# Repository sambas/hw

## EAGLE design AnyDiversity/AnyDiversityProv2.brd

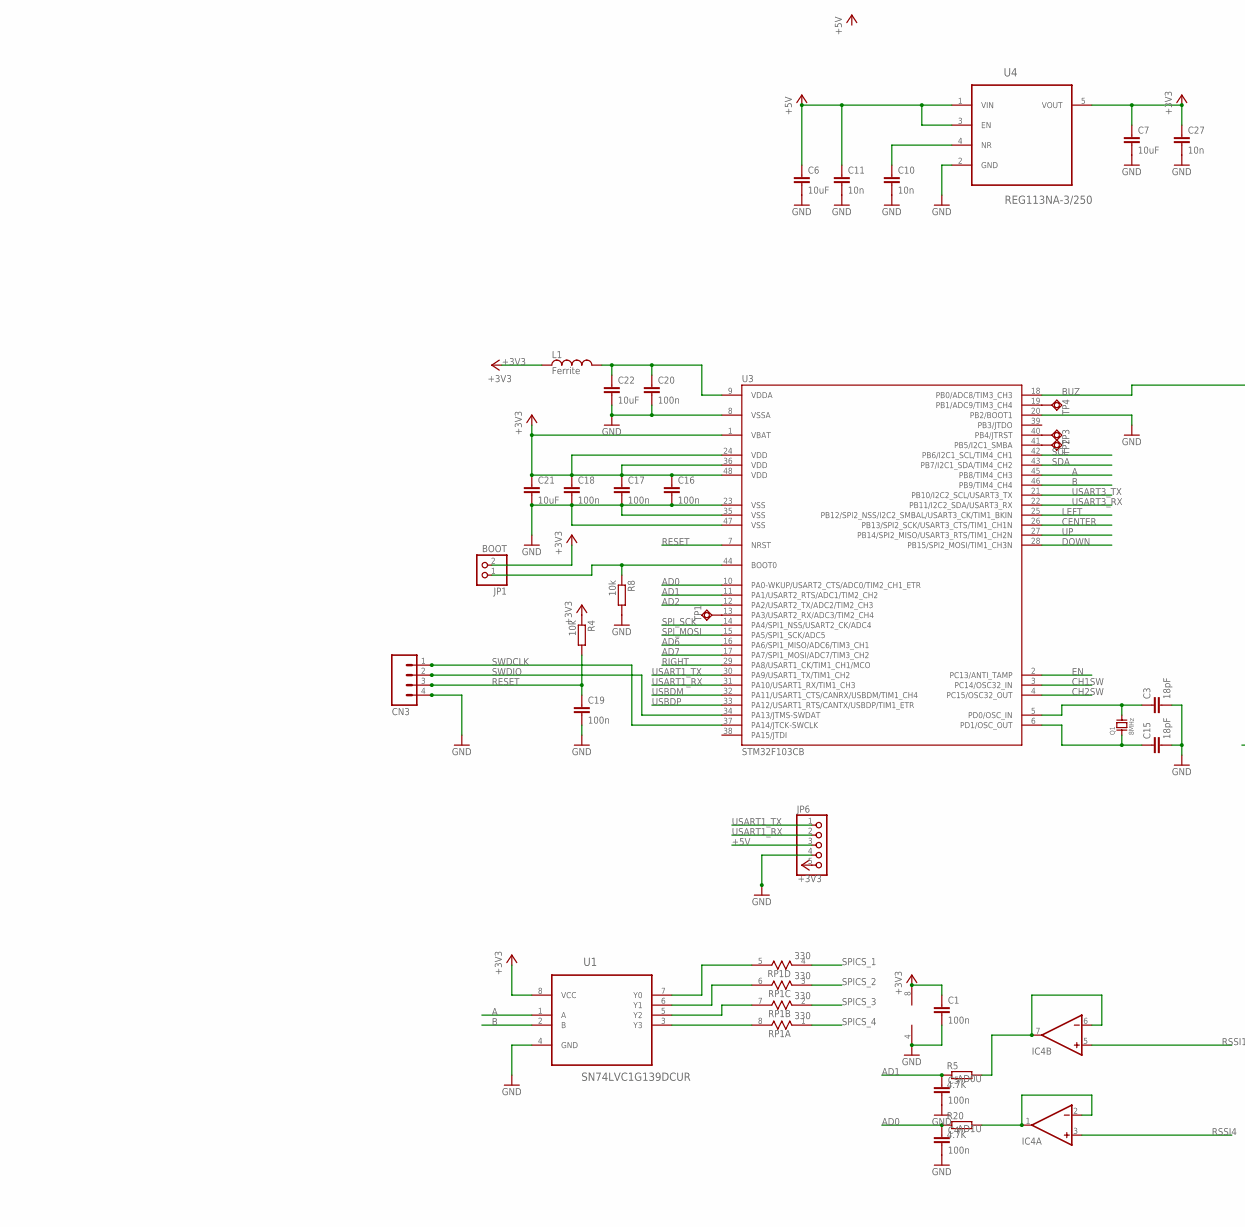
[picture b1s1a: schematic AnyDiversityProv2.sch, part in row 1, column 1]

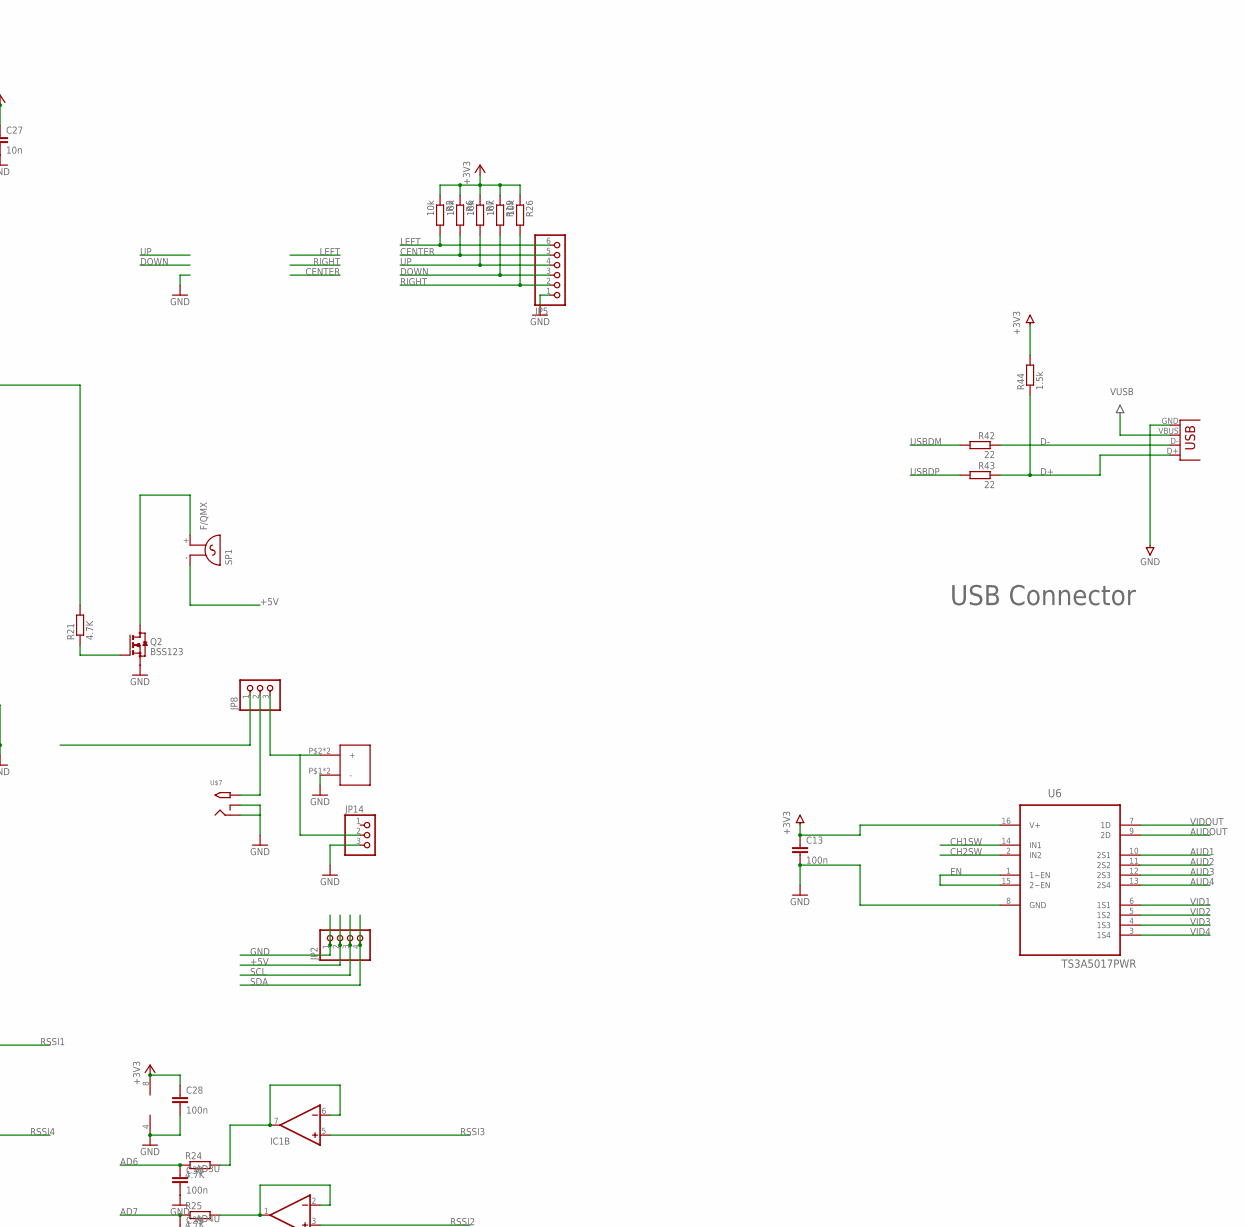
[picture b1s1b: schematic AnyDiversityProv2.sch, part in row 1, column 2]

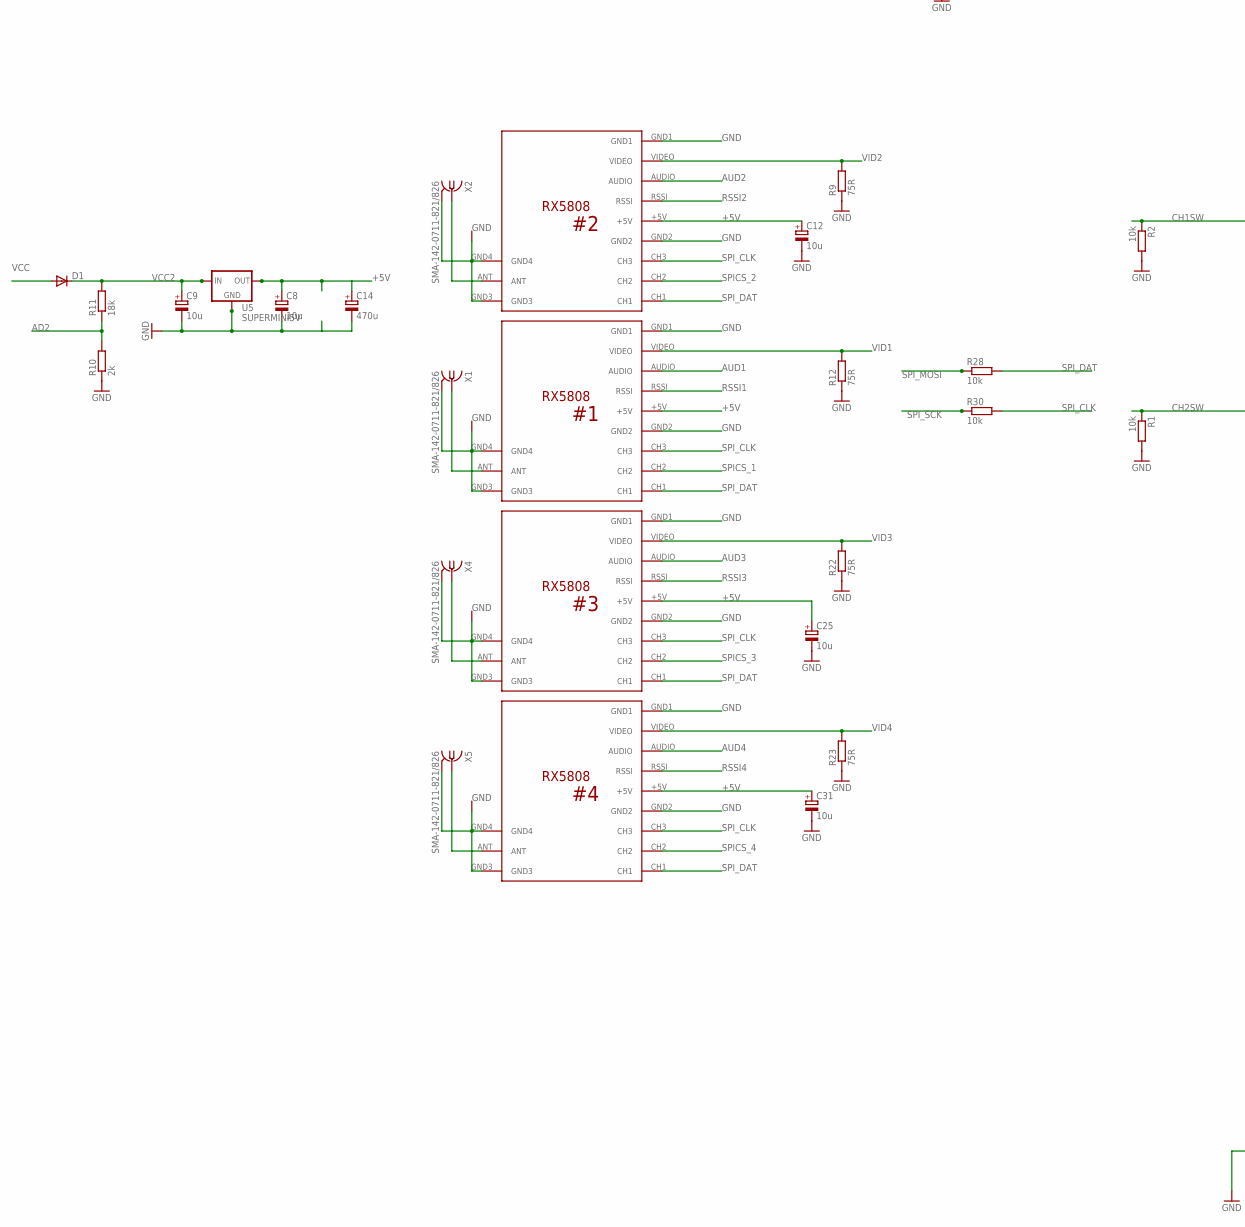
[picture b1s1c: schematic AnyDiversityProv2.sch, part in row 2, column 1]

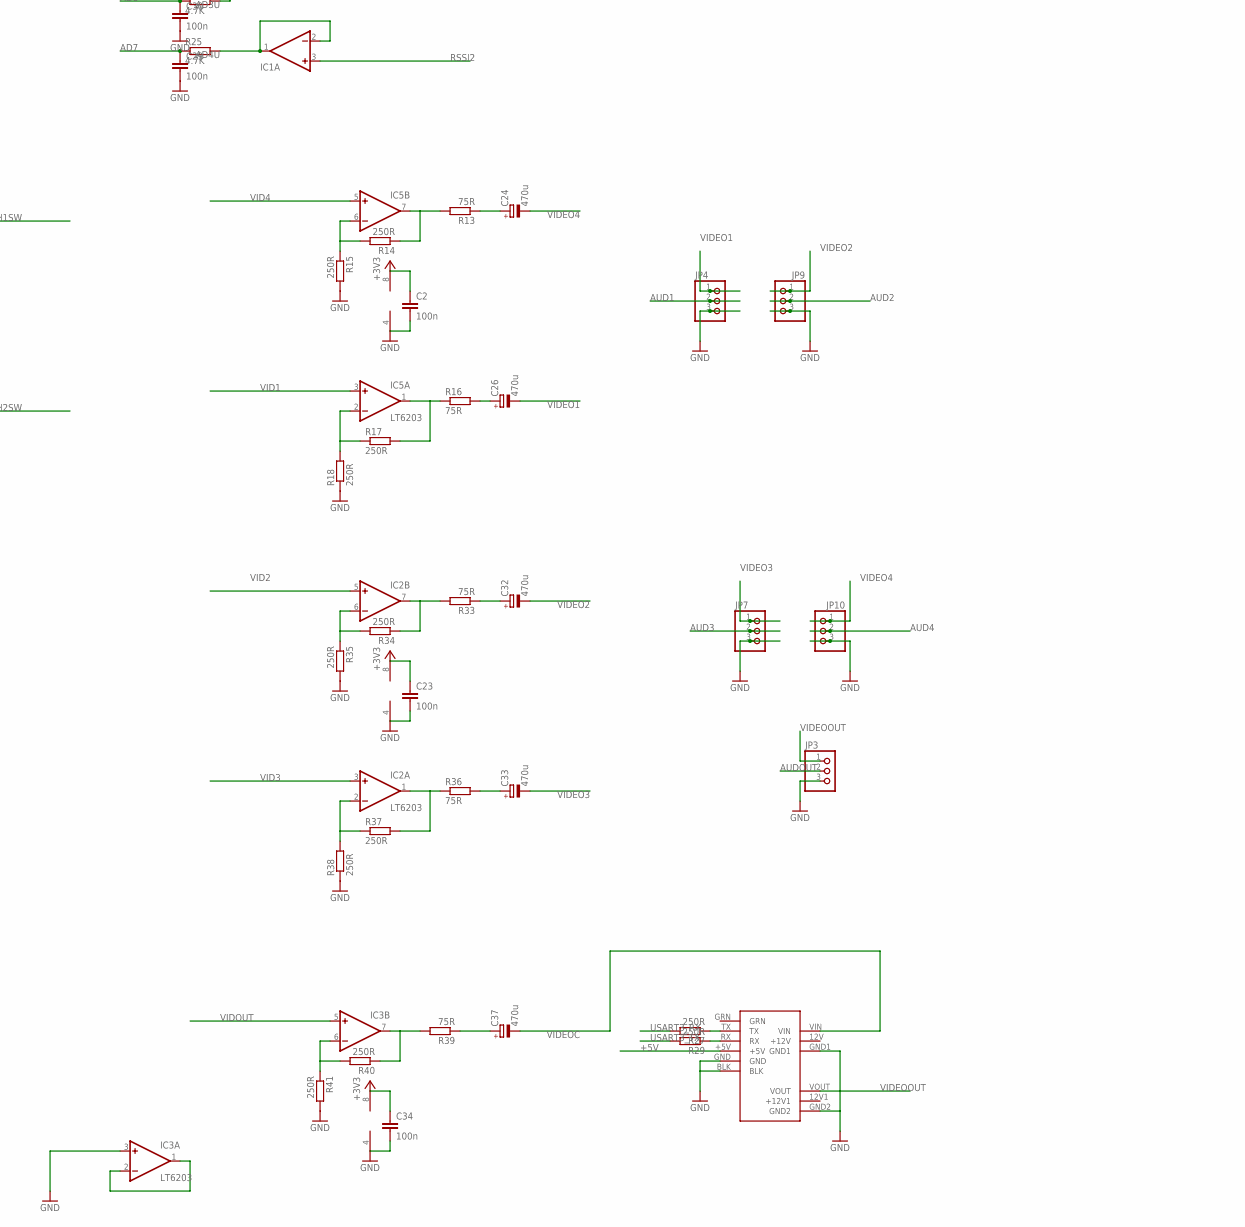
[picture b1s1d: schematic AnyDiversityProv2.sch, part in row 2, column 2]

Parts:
C1, C2, C4, C5, C13, C16, C17, C18, C19, C20, C23, C28, C29, C30, C34: 100n; C0603K
C3, C15: 18pF; 0603
C6, C7, C21, C22: 10uF; C0805K
C8, C9, C12, C25, C31: 10u; A/3216-18W
C10, C11, C27: 10n; C0603K
C14, C24, C26, C32, C33, C37: 470u; PANASONIC_E
CN3: SM04B-SRSS-TB
D1: DIODE-DO214AA; DO214AA
IC1, IC4: LMV358; SO08
IC2, IC3, IC5: LT6203; SO08
JP1: BOOT; 1X02-S
JP2: PINHD-1X04_2.54-S; 1X04-S
JP3, JP4, JP7, JP8, JP9, JP10, JP14: PINHD-1X03_2.54-S; 1X03-S
JP5: PINHD-1X06_2.00; 1X06M
JP6: PINHD-1X05_2.54-S; 1X05-S
L1: Ferrite; 0603
Q1: 8MHz; CRYSTAL-5X3
Q2: BSS123; SOT23
R1, R2, R3, R4, R6, R7, R8, R19, R26, R28, R30: 10k; R0603
R5, R20, R21, R24, R25: 4.7K; R0603
R9, R12, R13, R16, R22, R23, R33, R36, R39: 75R; R0603
R10: 2k; R0603
R11: 18k; R0603
R14, R15, R17, R18, R27, R29, R34, R35, R37, R38, R40, R41: 250R; R0603
R42, R43: 22; R0603
R44: 1.5k; R0603
RP1: 330; RES4NT
SP1: F/QMX
TP1, TP2, TP3, TP4: TPSQB1,27; B1,27
U1: SN74LVC1G139DCUR; SOP50P310X90-8N
U3: STM32F103CB; LQFP48
U4: REG113NA-3/250; SOT95P280X145-5N
U5: SUPERMINI5V
U6: TS3A5017PWR; SOP65P640X120-16N
U$1, U$2, U$3, U$4: 1CUSTOMSTUFF_RX5808
U$5: MINIMOSD
U$6: XT60
U$7: 2.1MMJACKTHM; PJ-102A
X1, X2, X4, X5: SMA-142-0711-821/826; J502-ND-142-0711-821/826
X3: USBSMD; USB-MINIB

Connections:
+3V3: C1.1, C2.1, C7.1, C13.1, C16.1, C17.1, C18.1, C21.1, C23.1, C27.1, C28.1, C34.1, IC1.8 (V+), IC2.8 (V+), IC3.8 (V+), IC4.8 (V+), IC5.8 (V+), JP1.2, JP6.5, L1.1, R3.1, R4.1, R6.1, R7.1, R19.1, R26.1, R44.2, U1.8 (VCC), U3.1 (VBAT), U3.24 (VDD), U3.36 (VDD), U3.48 (VDD), U4.5 (VOUT), U6.16 (V+)
+5V: C6.1, C8.+, C11.1, C12.+, C14.+, C25.+, C31.+, JP2.2, JP6.3, JP8.1, SP1.- (1), U4.1 (VIN), U4.3 (EN), U5.1 (OUT), U5.2 (OUT1), U$1.+5V, U$2.+5V, U$3.+5V, U$4.+5V, U$5.+5V
A: U1.1 (A), U3.45 (PB8/TIM4_CH3)
AD0: C4.1, R20.1, U3.10 (PA0-WKUP/USART2_CTS/ADC0/TIM2_CH1_ETR)
AD0U: IC4.6 (-IN), IC4.7 (OUT), R5.2
AD1: C5.1, R5.1, U3.11 (PA1/USART2_RTS/ADC1/TIM2_CH2)
AD1U: IC4.1 (OUT), IC4.2 (-IN), R20.2
AD2: R10.2, R11.1, U3.12 (PA2/USART2_TX/ADC2/TIM2_CH3)
AD3U: IC1.6 (-IN), IC1.7 (OUT), R24.2
AD4U: IC1.1 (OUT), IC1.2 (-IN), R25.2
AD6: C30.1, R24.1, U3.16 (PA6/SPI1_MISO/ADC6/TIM3_CH1)
AD7: C29.1, R25.1, U3.17 (PA7/SPI1_MOSI/ADC7/TIM3_CH2)
ANT: U$3.ANT, X2.1
ANT1: U$2.ANT, X1.1
ANT2: U$1.ANT, X4.1
ANT3: U$4.ANT, X5.1
AUD1: JP4.2, U6.10 (2S1), U$2.AUDIO
AUD2: JP9.2, U6.11 (2S2), U$3.AUDIO
AUD3: JP7.2, U6.12 (2S3), U$1.AUDIO
AUD4: JP10.2, U6.13 (2S4), U$4.AUDIO
AUDOUT: JP3.2, U6.9 (2D)
B: U1.2 (B), U3.46 (PB9/TIM4_CH4)
BUZ: R21.2, U3.18 (PB0/ADC8/TIM3_CH3)
CENTER: JP5.5, R6.2, U3.26 (PB13/SPI2_SCK/USART3_CTS/TIM1_CH1N)
CH1SW: R2.1, U3.3 (PC14/OSC32_IN), U6.14 (IN1)
CH2SW: R1.1, U3.4 (PC15/OSC32_OUT), U6.2 (IN2)
D+: R43.1, R44.1, X3.D+
D-: R42.1, X3.D-
DOWN: JP5.3, R19.2, U3.28 (PB15/SPI2_MOSI/TIM1_CH3N)
EN: U3.2 (PC13/ANTI_TAMP), U6.1 (1~EN), U6.15 (2~EN)
GND: C1.2, C2.2, C3.2, C4.2, C5.2, C6.2, C7.2, C8.-, C9.-, C10.2, C11.2, C12.-, C13.2, C14.-, C15.2, C16.2, C17.2, C18.2, C19.2, C20.2, C21.2, C22.2, C23.2, C25.-, C27.2, C28.2, C29.2, C30.2, C31.-, C34.2, CN3.4, IC1.4 (V-), IC2.4 (V-), IC3.3 (+IN), IC3.4 (V-), IC4.4 (V-), IC5.4 (V-), JP2.1, JP3.3, JP4.3, JP5.1, JP6.4, JP7.3, JP9.3, JP10.3, JP14.3, Q2.2 (S), R1.2, R2.2, R8.2, R9.1, R10.1, R12.1, R15.2, R18.1, R22.1, R23.1, R35.2, R38.1, R41.2, U1.4 (GND), U3.8 (VSSA), U3.20 (PB2/BOOT1), U3.23 (VSS), U3.35 (VSS), U3.47 (VSS), U4.2 (GND), U5.5 (GND), U5.6 (GND1), U5.7 (GND2), U5.8 (GND3), U6.8 (GND), U$1.GND1, U$1.GND2, U$1.GND3, U$1.GND4, U$2.GND1, U$2.GND2, U$2.GND3, U$2.GND4, U$3.GND1, U$3.GND2, U$3.GND3, U$3.GND4, U$4.GND1, U$4.GND2, U$4.GND3, U$4.GND4, U$5.BLK, U$5.GND, U$5.GND1, U$5.GND2, U$6.P$1 (-), U$6.P$3 (-), U$7.RING, U$7.RING_SW, X1.G@1 (2), X1.G@2 (2), X1.G@3 (2), X1.G@4 (2), X2.G@1 (2), X2.G@2 (2), X2.G@3 (2), X2.G@4 (2), X3.GND, X4.G@1 (2), X4.G@2 (2), X4.G@3 (2), X4.G@4 (2), X5.G@1 (2), X5.G@2 (2), X5.G@3 (2), X5.G@4 (2)
LEFT: JP5.6, R3.2, U3.25 (PB12/SPI2_NSS/I2C2_SMBAL/USART3_CK/TIM1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)
unnamed: C26.+, R16.2
unnamed: C24.+, R13.1
unnamed: C10.1, U4.4 (NR)
unnamed: Q2.1 (G), R21.1
unnamed: Q2.3 (D), SP1.+ (2)
unnamed: RP1.5 (2), U1.7 (Y0)
unnamed: RP1.6 (2), U1.6 (Y1)
unnamed: IC2.6 (-IN), R34.2, R35.1
unnamed: IC2.7 (OUT), R33.2, R34.1
unnamed: IC2.2 (-IN), R37.1, R38.2
unnamed: IC2.1 (OUT), R36.1, R37.2
unnamed: RP1.7 (2), U1.5 (Y2)
unnamed: C33.+, R36.2
unnamed: RP1.8 (2), U1.3 (Y3)
unnamed: C32.+, R33.1
unnamed: R29.1, U$5.RX
unnamed: R27.1, U$5.TX
unnamed: IC5.6 (-IN), R14.2, R15.1
unnamed: IC3.6 (-IN), R40.2, R41.1
unnamed: IC5.7 (OUT), R13.2, R14.1
unnamed: IC5.2 (-IN), R17.1, R18.2
unnamed: IC5.1 (OUT), R16.1, R17.2
unnamed: C20.1, C22.1, L1.2, U3.9 (VDDA)
unnamed: JP1.1, R8.1, U3.44 (BOOT0)
unnamed: IC3.7 (OUT), R39.2, R40.1
unnamed: IC3.1 (OUT), IC3.2 (-IN)
unnamed: JP8.2, U$7.TIP
unnamed: C3.1, Q1.3 (2), U3.5 (PD0/OSC_IN)
unnamed: C37.+, R39.1
unnamed: C15.1, Q1.1, U3.6 (PD1/OSC_OUT)
unnamed: TP1.TP, U3.13 (PA3/USART2_RX/ADC3/TIM2_CH4)
unnamed: TP3.TP, U3.40 (PB4/JTRST)
unnamed: TP4.TP, U3.19 (PB1/ADC9/TIM3_CH4)
unnamed: TP2.TP, U3.41 (PB5/I2C1_SMBA)
RESET: C19.1, CN3.3, R4.2, U3.7 (NRST)
RIGHT: JP5.2, R26.2, U3.29 (PA8/USART1_CK/TIM1_CH1/MCO)
RSSI1: IC4.5 (+IN), U$2.RSSI
RSSI2: IC1.3 (+IN), U$3.RSSI
RSSI3: IC1.5 (+IN), U$1.RSSI
RSSI4: IC4.3 (+IN), U$4.RSSI
SCL: JP2.3, U3.42 (PB6/I2C1_SCL/TIM4_CH1)
SDA: JP2.4, U3.43 (PB7/I2C1_SDA/TIM4_CH2)
SPICS_1: RP1.4 (1), U$2.CH2
SPICS_2: RP1.3 (1), U$3.CH2
SPICS_3: RP1.2 (1), U$1.CH2
SPICS_4: RP1.1, U$4.CH2
SPI_CLK: R30.2, U$1.CH3, U$2.CH3, U$3.CH3, U$4.CH3
SPI_DAT: R28.2, U$1.CH1, U$2.CH1, U$3.CH1, U$4.CH1
SPI_MOSI: R28.1, U3.15 (PA5/SPI1_SCK/ADC5)
SPI_SCK: R30.1, U3.14 (PA4/SPI1_NSS/USART2_CK/ADC4)
SWDCLK: CN3.1, U3.37 (PA14/JTCK-SWCLK)
SWDIO: CN3.2, U3.34 (PA13/JTMS-SWDAT)
UP: JP5.4, R7.2, U3.27 (PB14/SPI2_MISO/USART3_RTS/TIM1_CH2N)
USART1_RX: JP6.2, U3.31 (PA10/USART1_RX/TIM1_CH3)
USART1_TX: JP6.1, U3.30 (PA9/USART1_TX/TIM1_CH2)
USART3_RX: R27.2, U3.22 (PB11/I2C2_SDA/USART3_RX)
USART3_TX: R29.2, U3.21 (PB10/I2C2_SCL/USART3_TX)
USBDM: R42.2, U3.32 (PA11/USART1_CTS/CANRX/USBDM/TIM1_CH4)
USBDP: R43.2, U3.33 (PA12/USART1_RTS/CANTX/USBDP/TIM1_ETR)
VCC: D1.A, JP8.3, JP14.2, U$6.P$2 (+), U$6.P$4 (+)
VCC2: C9.+, D1.C, R11.2, U5.3 (IN), U5.4 (IN1)
VID1: IC5.3 (+IN), R12.2, U6.6 (1S1), U$2.VIDEO
VID2: IC2.5 (+IN), R9.2, U6.5 (1S2), U$3.VIDEO
VID3: IC2.3 (+IN), R22.2, U6.4 (1S3), U$1.VIDEO
VID4: IC5.5 (+IN), R23.2, U6.3 (1S4), U$4.VIDEO
VIDEO1: C26.-, JP4.1
VIDEO2: C32.-, JP9.1
VIDEO3: C33.-, JP7.1
VIDEO4: C24.-, JP10.1
VIDEOC: C37.-, U$5.VIN
VIDEOOUT: JP3.1, U$5.VOUT
VIDOUT: IC3.5 (+IN), U6.7 (1D)
VUSB: X3.VBUS

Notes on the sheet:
USB Connector

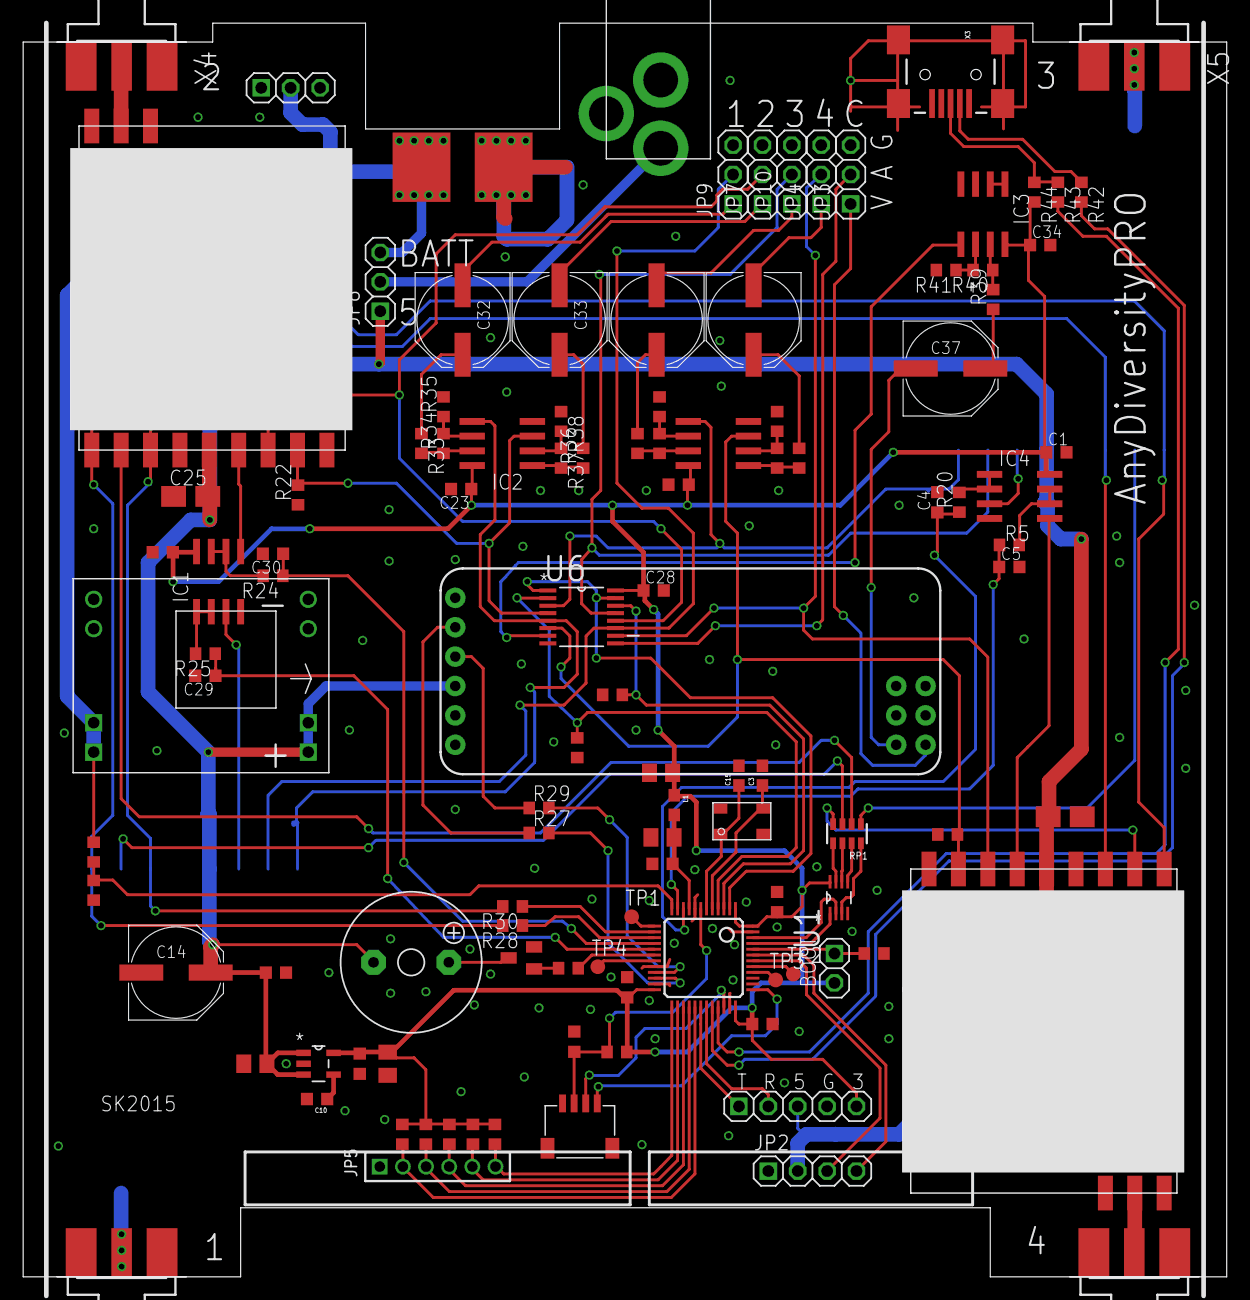
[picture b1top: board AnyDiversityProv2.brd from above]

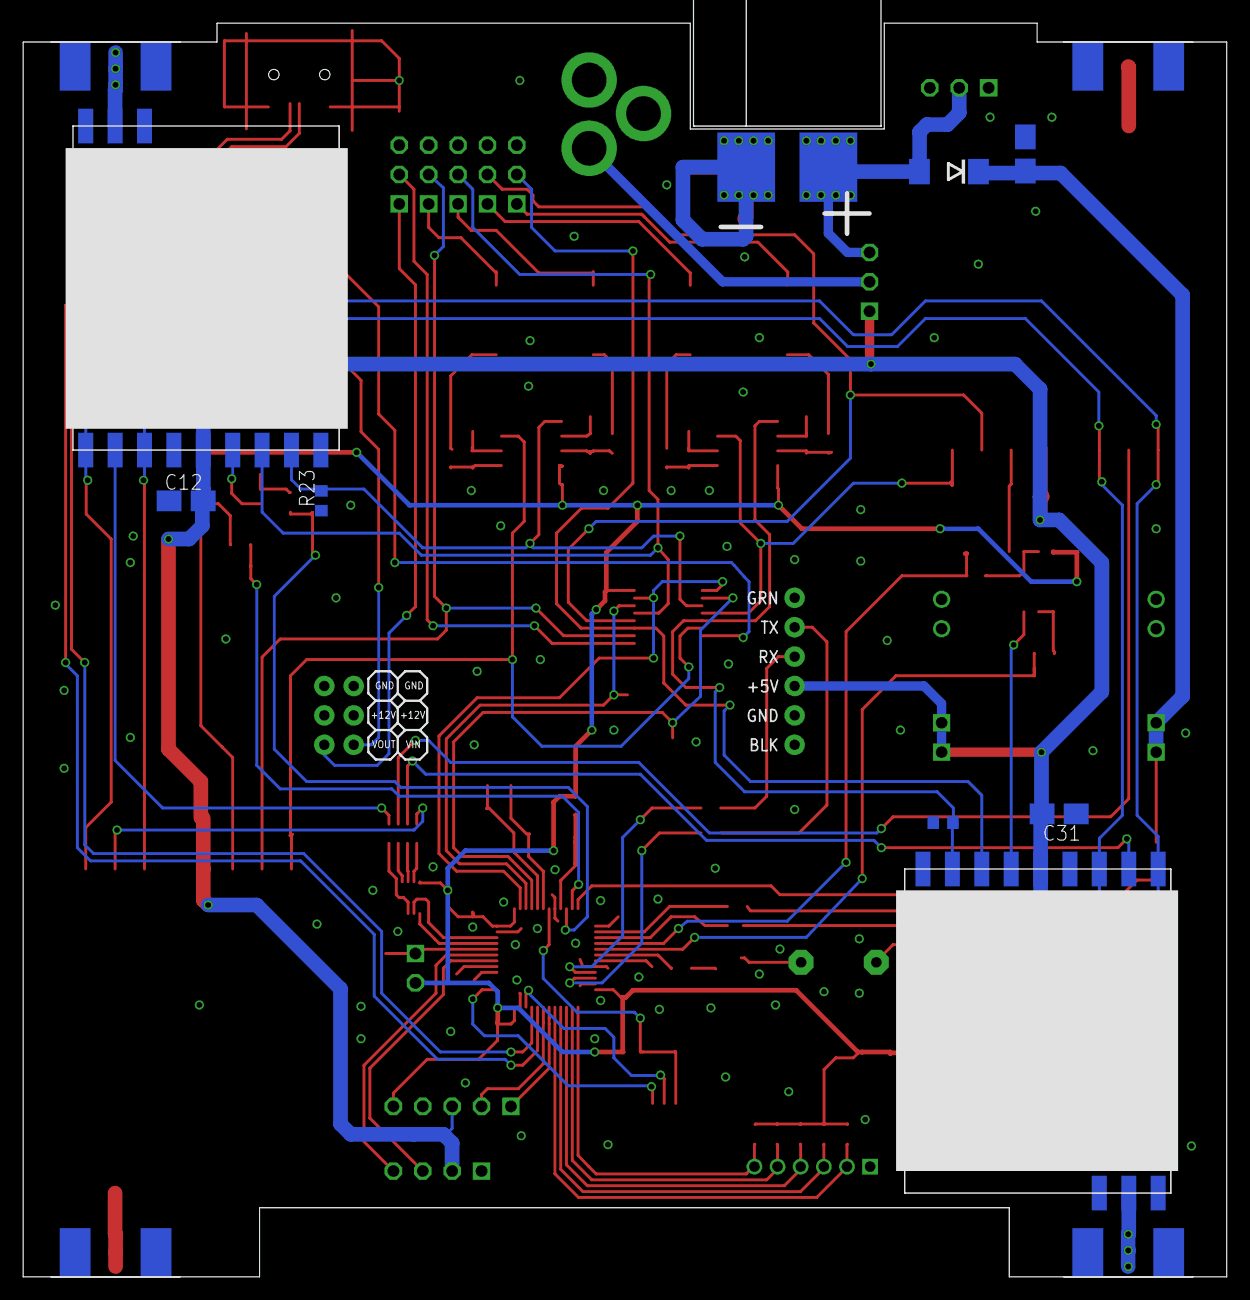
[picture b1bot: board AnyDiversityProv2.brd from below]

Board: 4 copper layers, 104.0 x 108.3 mm, 121 parts (9 on the bottom side), 104 nets.

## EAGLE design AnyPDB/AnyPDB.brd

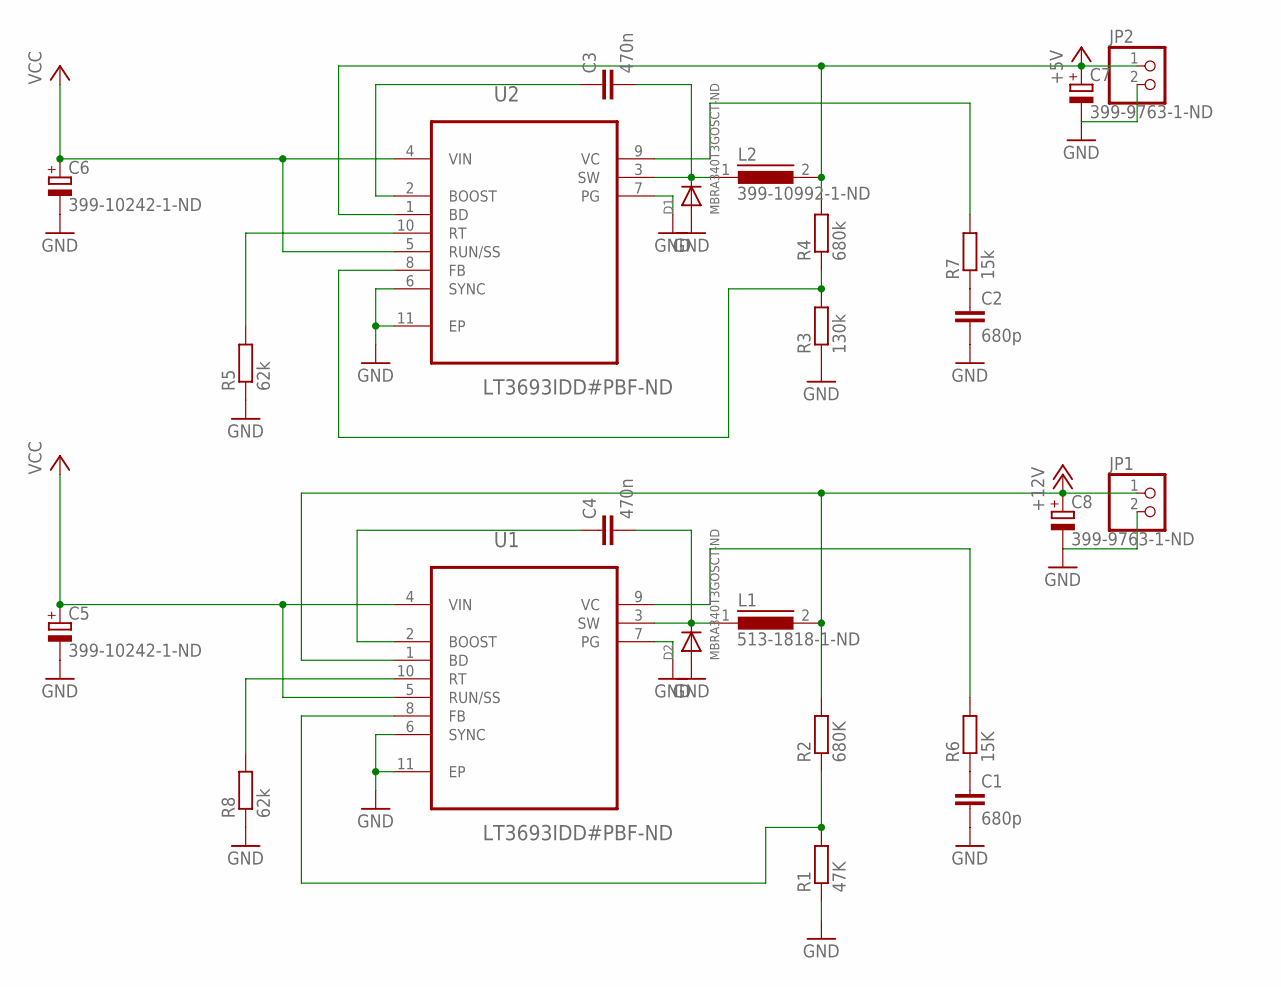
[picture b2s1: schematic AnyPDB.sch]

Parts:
C1, C2: 680p; C0402K
C3, C4: 470n; C0402K
C5, C6: 399-10242-1-ND; CT6032
C7, C8: 399-9763-1-ND; CT6032
D1, D2: MBRA340T3GOSCT-ND; SMADIODE
JP1, JP2: PINHD-1X02_2.54-S; 1X02-S
L1: 513-1818-1-ND; DR74
L2: 399-10992-1-ND; DR74
R1: 47K; R0402
R2: 680K; R0402
R3: 130k; R0402
R4: 680k; R0402
R5, R8: 62k; R0402
R6: 15K; R0402
R7: 15k; R0402
U1, U2: LT3693IDD#PBF-ND; DFN300X300X80-11N

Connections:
+5V: C7.+, JP2.1, L2.2, R4.2, U2.1 (BD)
+12V: C8.+, JP1.1, L1.2, R2.2, U1.1 (BD)
GND: C1.2, C2.2, C5.-, C6.-, C7.-, C8.-, D1.A, D2.A, JP1.2, JP2.2, R1.1, R3.1, R5.1, R8.1, U1.6 (SYNC), U1.7 (PG), U1.11 (EP), U2.6 (SYNC), U2.7 (PG), U2.11 (EP)
unnamed: R1.2, R2.1, U1.8 (FB)
unnamed: R3.2, R4.1, U2.8 (FB)
unnamed: C4.2, D2.C, L1.1, U1.3 (SW)
unnamed: C3.2, D1.C, L2.1, U2.3 (SW)
unnamed: R5.2, U2.10 (RT)
unnamed: R7.2, U2.9 (VC)
unnamed: R6.2, U1.9 (VC)
unnamed: R8.2, U1.10 (RT)
unnamed: C1.1, R6.1
unnamed: C2.1, R7.1
unnamed: C4.1, U1.2 (BOOST)
unnamed: C3.1, U2.2 (BOOST)
VCC: C5.+, C6.+, U1.4 (VIN), U1.5 (RUN/SS), U2.4 (VIN), U2.5 (RUN/SS)

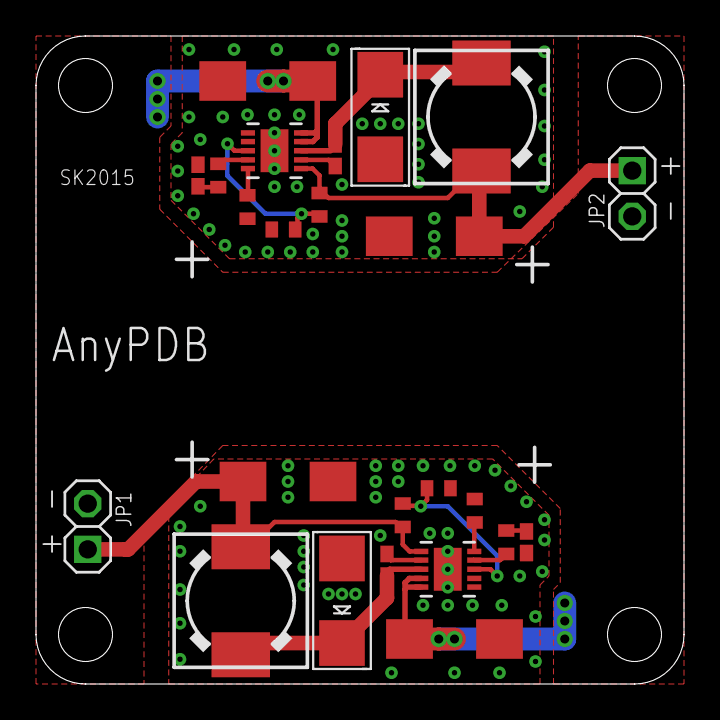
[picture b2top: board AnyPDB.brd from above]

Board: 2 copper layers, 36.0 x 36.0 mm, 24 parts (0 on the bottom side), 16 nets.

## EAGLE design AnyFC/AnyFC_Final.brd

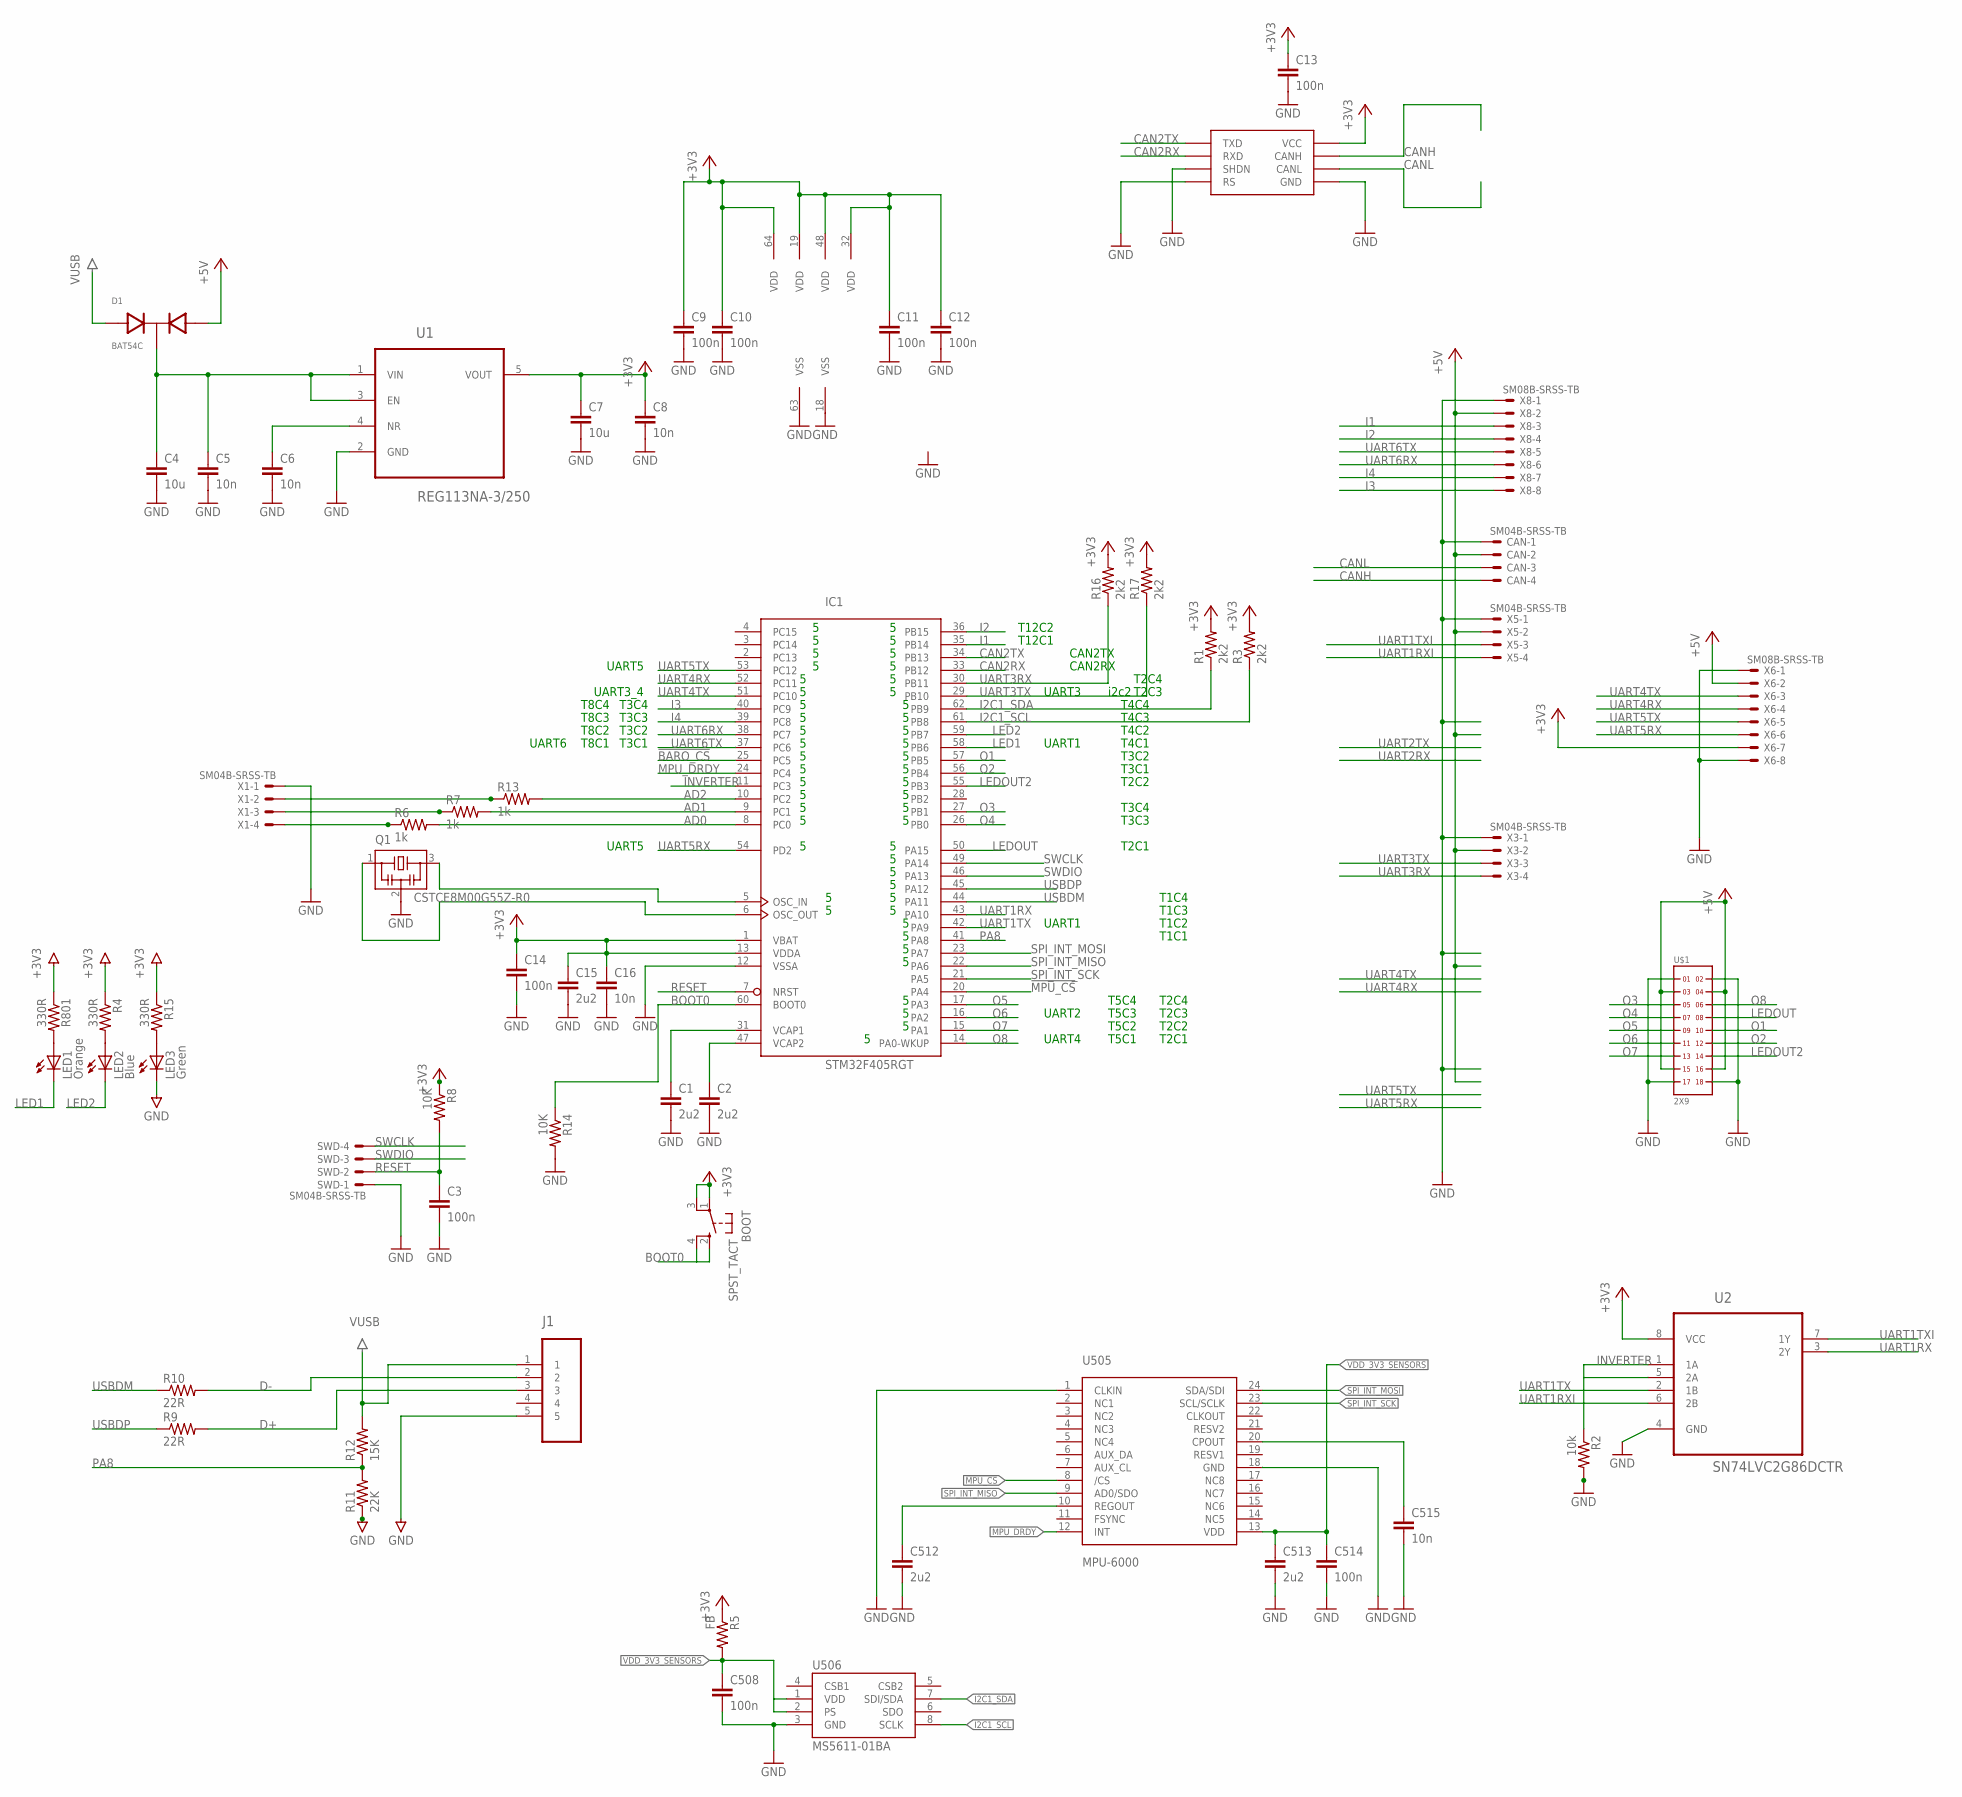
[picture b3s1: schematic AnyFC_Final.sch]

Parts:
BOOT: SPST_TACT; EVQ-PU
C1, C2, C15, C512, C513: 2u2; 0603-CAP; PARTNO C1608X6S1C225K080AC
C3, C9, C10, C11, C12, C13, C14: 100n; 0402-CAP; PARTNO C1608X6S1C225K080AC
C4, C7: 10u; 0805-CAP; PARTNO C1608X6S1C225K080AC
C5, C6, C8, C16: 10n; 0402-CAP; PARTNO C1608X6S1C225K080AC
C508, C514: 100n; 0402-CAP; PARTNO CC0402ZRY5V7BB104
C515: 10n; 0402-CAP; PARTNO 06033C103JAT2A
CAN: SM04B-SRSS-TB
D1: BAT54C; SOT23
IC1: STM32F405RGT; LQFP64
J1: 47346-0001; MOLEX_47346-0001
LED1: Orange; CHIPLED_0603
LED2: Blue; CHIPLED_0603
LED3: Green; CHIPLED_0603
Q1: CSTCE8M00G55Z-R0; CSTER12M
R1, R3, R16, R17: 2k2; 0402-RES; PARTNO RC0402FR-0710KL
R2: 10k; 0402-RES; PARTNO RC0402FR-0710KL
R4, R15, R801: 330R; 0402-RES; PARTNO RC0402FR-0710KL
R5: FB; 0603-RES; PARTNO RC0402FR-0710KL
R6, R7, R13: 1k; 0402-RES; PARTNO RC0402FR-0710KL
R8, R14: 10K; 0402-RES; PARTNO RC0402FR-0710KL
R9, R10: 22R; 0402-RES; PARTNO RC0402FR-0710KL
R11: 22K; 0402-RES; PARTNO RC0402FR-0710KL
R12: 15K; 0402-RES; PARTNO RC0402FR-0710KL
SWD: SM04B-SRSS-TB
U1: REG113NA-3/250; SOT95P280X145-5N
U2: SN74LVC2G86DCTR; SOP65P400X130-8N
U3: MAX3051EKA; SOT23-8L
U505: MPU-6000; QFN-24; PARTNO MPU-6000
U506: MS5611-01BA; PARTNO MS5611-01BA
U$1: 2X9
X1, X3, X5: SM04B-SRSS-TB
X6, X8: SM08B-SRSS-TB

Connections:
!BARO_CS: IC1.25 (PC5)
!MPU_CS: IC1.20 (PA4), U505.8 (/CS)
+3V3: BOOT.1, BOOT.3 (P1), C7.P$1 (1), C8.P$1 (1), C9.P$1 (1), C10.P$1 (1), C11.P$1 (1), C12.P$1 (1), C13.P$1 (1), C14.P$1 (1), C15.P$1 (1), C16.P$1 (1), IC1.1 (VBAT), IC1.13 (VDDA), IC1.19 (VDD), IC1.32 (VDD), IC1.48 (VDD), IC1.64 (VDD), R1.P$2 (2), R3.P$2 (2), R4.P$1 (1), R5.1, R8.P$1 (1), R15.P$1 (1), R16.P$2 (2), R17.P$2 (2), R801.P$1 (1), U1.5 (VOUT), U2.8 (VCC), U3.3 (VCC), X6.7
+5V: CAN.2, D1.2, U$1.3, U$1.4, U$1.15, U$1.16, X3.2, X5.2, X6.2, X8.2
AD0: IC1.8 (PC0), R6.P$2 (2)
AD1: IC1.9 (PC1), R7.P$2 (2)
AD2: IC1.10 (PC2), R13.P$2 (2)
BOOT0: BOOT.2 (S), BOOT.4 (S1), IC1.60 (BOOT0), R14.P$1 (1)
CAN2RX: IC1.33 (PB12), U3.4 (RXD)
CAN2TX: IC1.34 (PB13), U3.1 (TXD)
CANH: CAN.4, U3.7 (CANH)
CANL: CAN.3, U3.6 (CANL)
D+: J1.3, R9.P$2 (2)
D-: J1.2, R10.P$2 (2)
GND: C1.P$2 (2), C2.P$2 (2), C3.P$2 (2), C4.P$2 (2), C5.P$2 (2), C6.P$2 (2), C7.P$2 (2), C8.P$2 (2), C9.P$2 (2), C10.P$2 (2), C11.P$2 (2), C12.P$2 (2), C13.P$2 (2), C14.P$2 (2), C15.P$2 (2), C16.P$2 (2), C508.P$2 (2), C512.P$2 (2), C513.P$2 (2), C514.P$2 (2), C515.P$2 (2), CAN.1, IC1.12 (VSSA), IC1.18 (VSS), IC1.63 (VSS), J1.5, LED3.C, Q1.2, R2.P$2 (2), R11.P$1 (1), R14.P$2 (2), SWD.1, U1.2 (GND), U2.4 (GND), U3.2 (GND), U3.5 (SHDN), U3.8 (RS), U505.1 (CLKIN), U505.18 (GND), U506.3 (GND), U$1.1, U$1.2, U$1.17, U$1.18, X1.1, X3.1, X5.1, X6.1, X6.8, X8.1
I1: IC1.35 (PB14), X8.3
I2: IC1.36 (PB15), X8.4
I2C1_SCL: IC1.61 (PB8), R3.P$1 (1), U506.8 (SCLK)
I2C1_SDA: IC1.62 (PB9), R1.P$1 (1), U506.7 (SDI/SDA)
I3: IC1.40 (PC9), X8.8
I4: IC1.39 (PC8), X8.7
INVERTER: IC1.11 (PC3), R2.P$1 (1), U2.1 (1A), U2.5 (2A)
LED1: IC1.58 (PB6), LED1.C
LED2: IC1.59 (PB7), LED2.C
LEDOUT: IC1.50 (PA15), U$1.8
LEDOUT2: IC1.55 (PB3), U$1.14
MPU_DRDY: IC1.24 (PC4), U505.12 (INT)
unnamed: C6.P$1 (1), U1.4 (NR)
unnamed: IC1.5 (OSC_IN), Q1.3
unnamed: C1.P$1 (1), IC1.31 (VCAP1)
unnamed: C2.P$1 (1), IC1.47 (VCAP2)
unnamed: IC1.6 (OSC_OUT), Q1.1
unnamed: LED1.A, R801.P$2 (2)
unnamed: LED3.A, R15.P$2 (2)
unnamed: LED2.A, R4.P$2 (2)
unnamed: R6.P$1 (1), X1.4
unnamed: R7.P$1 (1), X1.3
unnamed: R13.P$1 (1), X1.2
unnamed: C512.P$1 (1), U505.10 (REGOUT)
unnamed: C515.P$1 (1), U505.20 (CPOUT)
O1: IC1.57 (PB5), U$1.10
O2: IC1.56 (PB4), U$1.12
O3: IC1.27 (PB1), U$1.5
O4: IC1.26 (PB0), U$1.7
O5: IC1.17 (PA3), U$1.9
O6: IC1.16 (PA2), U$1.11
O7: IC1.15 (PA1), U$1.13
O8: IC1.14 (PA0-WKUP), U$1.6
PA8: IC1.41 (PA8), R11.P$2 (2), R12.P$1 (1)
RESET: C3.P$1 (1), IC1.7 (NRST), R8.P$2 (2), SWD.2
SPI_INT_MISO: IC1.22 (PA6), U505.9 (AD0/SDO)
SPI_INT_MOSI: IC1.23 (PA7), U505.24 (SDA/SDI)
SPI_INT_SCK: IC1.21 (PA5), U505.23 (SCL/SCLK)
SWCLK: IC1.49 (PA14), SWD.4
SWDIO: IC1.46 (PA13), SWD.3
UART1RX: IC1.43 (PA10), U2.3 (2Y)
UART1RXI: U2.6 (2B), X5.4
UART1TX: IC1.42 (PA9), U2.2 (1B)
UART1TXI: U2.7 (1Y), X5.3
UART3RX: IC1.30 (PB11), R16.P$1 (1), X3.4
UART3TX: IC1.29 (PB10), R17.P$1 (1), X3.3
UART4RX: IC1.52 (PC11), X6.4
UART4TX: IC1.51 (PC10), X6.3
UART5RX: IC1.54 (PD2), X6.6
UART5TX: IC1.53 (PC12), X6.5
UART6RX: IC1.38 (PC7), X8.6
UART6TX: IC1.37 (PC6), X8.5
USBDM: IC1.44 (PA11), R10.P$1 (1)
USBDP: IC1.45 (PA12), R9.P$1 (1)
V5: C4.P$1 (1), C5.P$1 (1), D1.3, U1.1 (VIN), U1.3 (EN)
VDD_3V3_SENSORS: C508.P$1 (1), C513.P$1 (1), C514.P$1 (1), R5.2, U505.13 (VDD), U506.1 (VDD), U506.2 (PS)
VUSB: D1.1, J1.1, R12.P$2 (2)

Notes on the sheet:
UART1
UART2
UART4
UART3
i2c2
UART6
UART3_4
UART5
T2C1
T5C1
T5C2
T5C3
T5C4
T2C4
T2C3
T2C2
T1C1
T1C2
T1C3
T1C4
T3C4
T3C3
T3C2
T3C1
T4C4
T4C3
T4C2
T4C1
T12C1
T12C2
CAN2RX
CAN2TX
T8C4
T8C3
T8C2
T8C1
